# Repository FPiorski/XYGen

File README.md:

# XYgen
### 4 digit numerical diplay using an oscilloscope in XY mode without a microcontroller

#### Work in progress
Soldered everything up, found some bugs, still working on getting them all fixed

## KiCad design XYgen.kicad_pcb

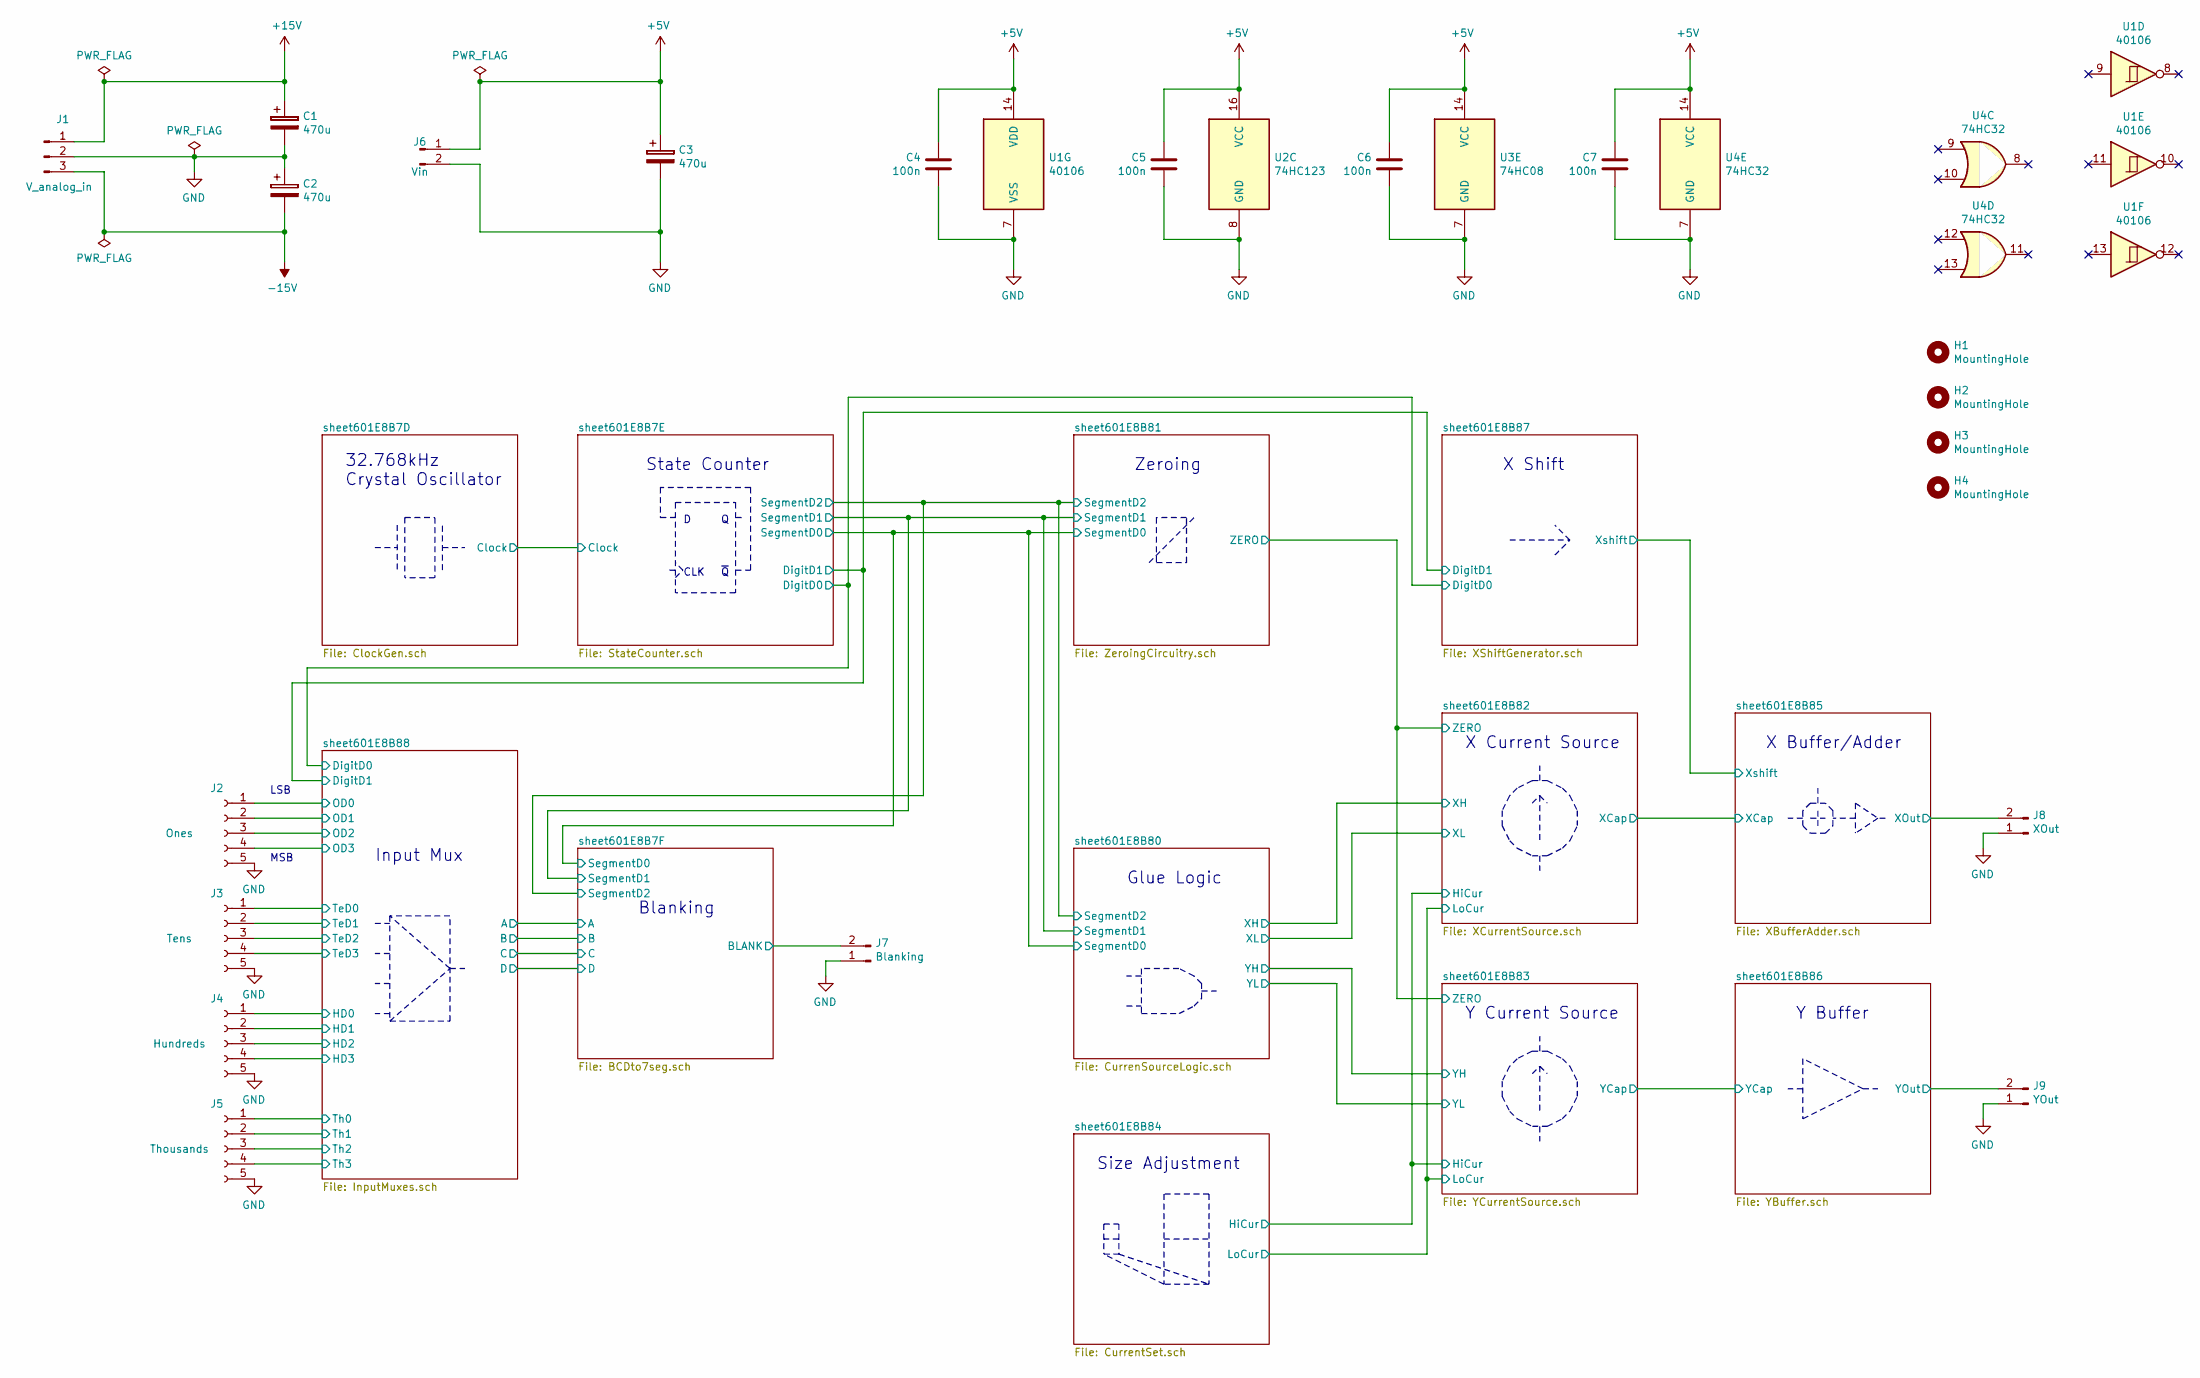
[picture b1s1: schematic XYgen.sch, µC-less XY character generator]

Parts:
C1, C2, C3: 470u; C_1206_3216Metric_Pad1.42x1.75mm_HandSolder
C4, C5, C6, C7: 100n; C_0805_2012Metric_Pad1.15x1.40mm_HandSolder
H1, H2, H3, H4: MountingHole; MountingHole_2.7mm_M2.5
J1: V_analog_in; Molex_KK-254_AE-6410-03A_1x03_P2.54mm_Vertical
J2: Ones; PinSocket_1x05_P2.54mm_Vertical
J3: Tens; PinSocket_1x05_P2.54mm_Vertical
J4: Hundreds; PinSocket_1x05_P2.54mm_Vertical
J5: Thousands; PinSocket_1x05_P2.54mm_Vertical
J6: Vin; Molex_KK-254_AE-6410-02A_1x02_P2.54mm_Vertical
J7: Blanking; PinHeader_1x02_P2.54mm_Vertical
J8: XOut; PinHeader_1x02_P2.54mm_Vertical
J9: YOut; PinHeader_1x02_P2.54mm_Vertical
U1: 40106; TSSOP-14_4.4x5mm_P0.65mm
U2: 74HC123; TSSOP-16_4.4x5mm_P0.65mm
U3: 74HC08; TSSOP-14_4.4x5mm_P0.65mm
U4: 74HC32; TSSOP-14_4.4x5mm_P0.65mm

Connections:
+5V: C3.1, C4.1, C5.1, C6.1, C7.1, J6.1, U1.14 (VDD), U2.16 (VCC), U3.14 (VCC), U4.14 (VCC); also elsewhere on the board
+15V: C1.1, J1.1; also elsewhere on the board
-15V: C2.2, J1.3; also elsewhere on the board
/sheet601E8B7F/BLANK: J7.2; also elsewhere on the board
/sheet601E8B85/XOut: J8.2; also elsewhere on the board
/sheet601E8B86/YOut: J9.2; also elsewhere on the board
/sheet601E8B88/HD0: J4.1; also elsewhere on the board
/sheet601E8B88/HD1: J4.2; also elsewhere on the board
/sheet601E8B88/HD2: J4.3; also elsewhere on the board
/sheet601E8B88/HD3: J4.4; also elsewhere on the board
/sheet601E8B88/OD0: J2.1; also elsewhere on the board
/sheet601E8B88/OD1: J2.2; also elsewhere on the board
/sheet601E8B88/OD2: J2.3; also elsewhere on the board
/sheet601E8B88/OD3: J2.4; also elsewhere on the board
/sheet601E8B88/TeD0: J3.1; also elsewhere on the board
/sheet601E8B88/TeD1: J3.2; also elsewhere on the board
/sheet601E8B88/TeD2: J3.3; also elsewhere on the board
/sheet601E8B88/TeD3: J3.4; also elsewhere on the board
/sheet601E8B88/Th0: J5.1; also elsewhere on the board
/sheet601E8B88/Th1: J5.2; also elsewhere on the board
/sheet601E8B88/Th2: J5.3; also elsewhere on the board
/sheet601E8B88/Th3: J5.4; also elsewhere on the board
GND: C1.2, C2.1, C3.2, C4.2, C5.2, C6.2, C7.2, J1.2, J2.5, J3.5, J4.5, J5.5, J6.2, J7.1, J8.1, J9.1, U1.7 (VSS), U2.8 (GND), U3.7 (GND), U4.7 (GND); also elsewhere on the board

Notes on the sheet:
32.768kHz Crystal Oscillator
CLK
State Counter
LSB
MSB
Zeroing
Input Mux
Blanking
X Shift
Glue Logic
Size Adjustment
X Current Source
Y Current Source
X Buffer/Adder
Y Buffer

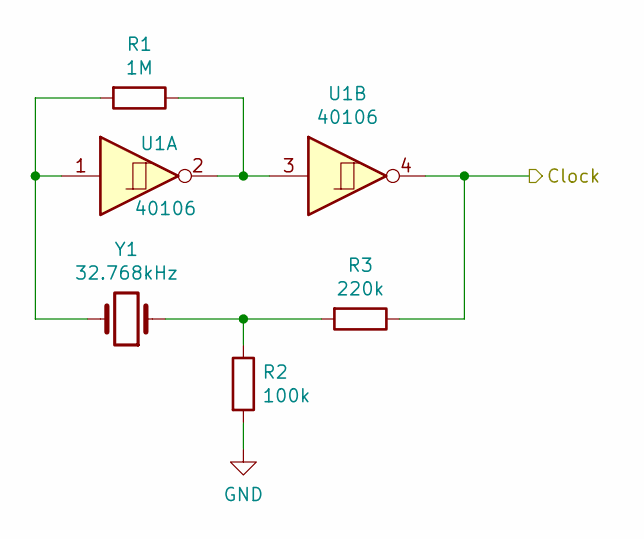
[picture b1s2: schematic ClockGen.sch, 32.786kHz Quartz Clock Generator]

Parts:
R1: 1M; R_0805_2012Metric_Pad1.15x1.40mm_HandSolder
R2: 100k; R_0805_2012Metric_Pad1.15x1.40mm_HandSolder
R3: 220k; R_0805_2012Metric_Pad1.15x1.40mm_HandSolder
U1: 40106; TSSOP-14_4.4x5mm_P0.65mm
Y1: 32.768kHz; Crystal_C26-LF_D2.1mm_L6.5mm_Vertical

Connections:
/sheet601E8B7D/Clock: R3.1, U1.4; also elsewhere on the board
GND: R2.2; also elsewhere on the board
unnamed: R1.1, U1.2, U1.3
unnamed: R1.2, U1.1, Y1.2
unnamed: R2.1, R3.2, Y1.1

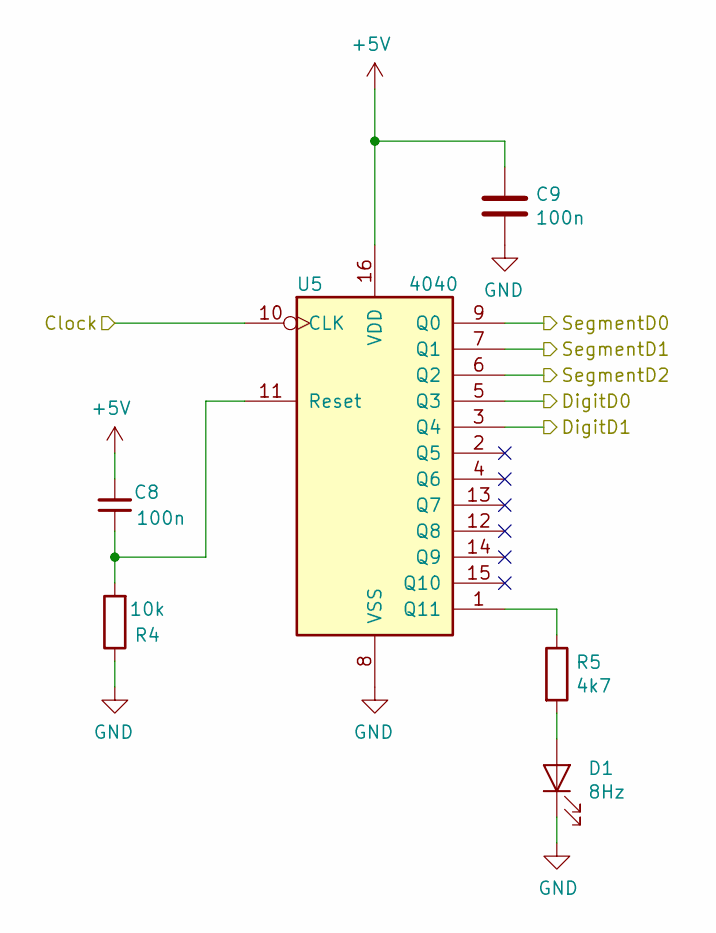
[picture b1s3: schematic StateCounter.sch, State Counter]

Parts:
C8, C9: 100n; C_0805_2012Metric_Pad1.15x1.40mm_HandSolder
D1: 8Hz; LED_0805_2012Metric_Pad1.15x1.40mm_HandSolder
R4: 10k; R_0805_2012Metric_Pad1.15x1.40mm_HandSolder
R5: 4k7; R_0805_2012Metric_Pad1.15x1.40mm_HandSolder
U5: 4040; TSSOP-16_4.4x5mm_P0.65mm

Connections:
+5V: C8.2, C9.1, U5.16 (VDD); also elsewhere on the board
/sheet601E8B7D/Clock: U5.10 (CLK); also elsewhere on the board
/sheet601E8B7E/DigitD0: U5.5 (Q3); also elsewhere on the board
/sheet601E8B7E/DigitD1: U5.3 (Q4); also elsewhere on the board
/sheet601E8B7E/SegmentD0: U5.9 (Q0); also elsewhere on the board
/sheet601E8B7E/SegmentD1: U5.7 (Q1); also elsewhere on the board
/sheet601E8B7E/SegmentD2: U5.6 (Q2); also elsewhere on the board
GND: C9.2, D1.1 (K), R4.1, U5.8 (VSS); also elsewhere on the board
unnamed: C8.1, R4.2, U5.11 (Reset)
unnamed: D1.2 (A), R5.2
unnamed: R5.1, U5.1 (Q11)

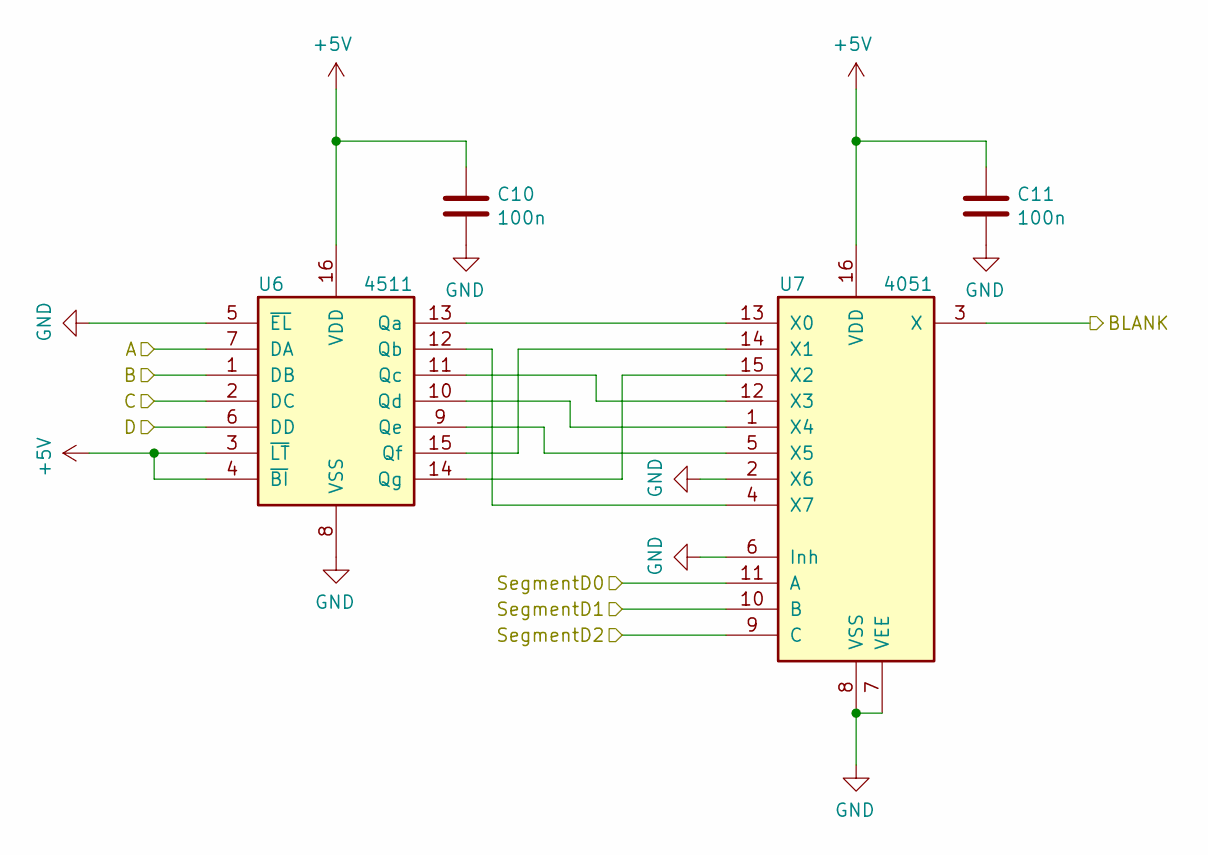
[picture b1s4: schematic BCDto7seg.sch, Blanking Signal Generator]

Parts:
C10, C11: 100n; C_0805_2012Metric_Pad1.15x1.40mm_HandSolder
U6: 4511; SOP-16_4.4x10.4mm_P1.27mm
U7: 4051; TSSOP-16_4.4x5mm_P0.65mm

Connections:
+5V: C10.1, C11.1, U6.3 (~LT), U6.4 (~BI), U6.16 (VDD), U7.16 (VDD); also elsewhere on the board
/sheet601E8B7E/SegmentD0: U7.11 (A); also elsewhere on the board
/sheet601E8B7E/SegmentD1: U7.10 (B); also elsewhere on the board
/sheet601E8B7E/SegmentD2: U7.9 (C); also elsewhere on the board
/sheet601E8B7F/A: U6.7 (DA); also elsewhere on the board
/sheet601E8B7F/B: U6.1 (DB); also elsewhere on the board
/sheet601E8B7F/BLANK: U7.3 (X); also elsewhere on the board
/sheet601E8B7F/C: U6.2 (DC); also elsewhere on the board
/sheet601E8B7F/D: U6.6 (DD); also elsewhere on the board
GND: C10.2, C11.2, U6.5 (~EL), U6.8 (VSS), U7.2 (X6), U7.6 (Inh), U7.7 (VEE), U7.8 (VSS); also elsewhere on the board
unnamed: U6.9 (Qe), U7.5 (X5)
unnamed: U6.10 (Qd), U7.1 (X4)
unnamed: U6.11 (Qc), U7.12 (X3)
unnamed: U6.12 (Qb), U7.4 (X7)
unnamed: U6.13 (Qa), U7.13 (X0)
unnamed: U6.14 (Qg), U7.15 (X2)
unnamed: U6.15 (Qf), U7.14 (X1)

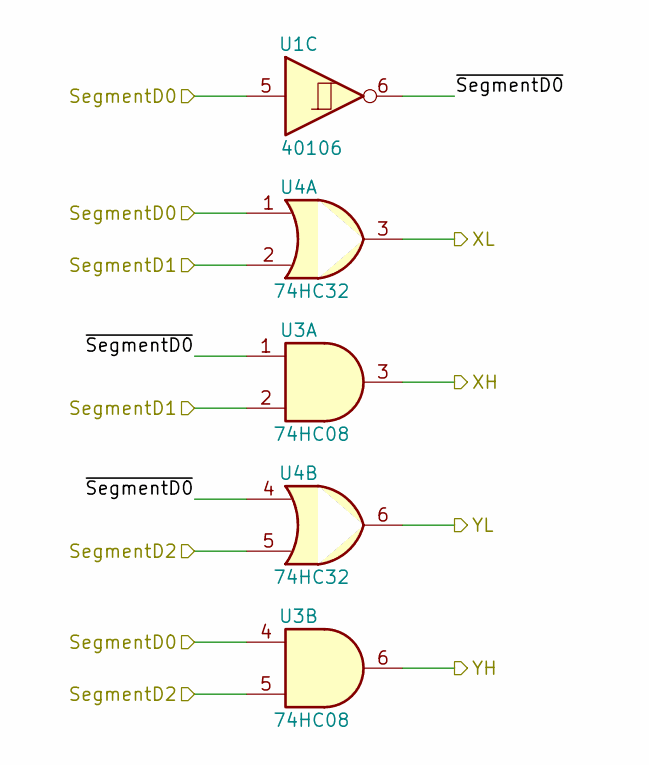
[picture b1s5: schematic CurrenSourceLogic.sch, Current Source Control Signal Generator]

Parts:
U1: 40106; TSSOP-14_4.4x5mm_P0.65mm
U3: 74HC08; TSSOP-14_4.4x5mm_P0.65mm
U4: 74HC32; TSSOP-14_4.4x5mm_P0.65mm

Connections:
/sheet601E8B7E/SegmentD0: U1.5, U3.4, U4.1; also elsewhere on the board
/sheet601E8B7E/SegmentD1: U3.2, U4.2; also elsewhere on the board
/sheet601E8B7E/SegmentD2: U3.5, U4.5; also elsewhere on the board
/sheet601E8B80/XH: U3.3; also elsewhere on the board
/sheet601E8B80/XL: U4.3; also elsewhere on the board
/sheet601E8B80/YH: U3.6; also elsewhere on the board
/sheet601E8B80/YL: U4.6; also elsewhere on the board
/sheet601E8B80/~SegmentD0: U1.6, U3.1, U4.4

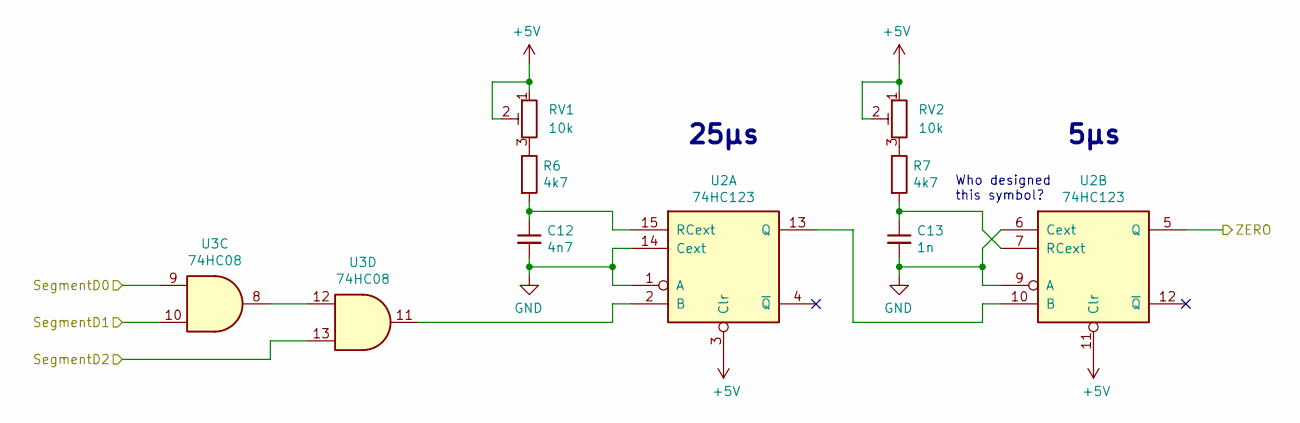
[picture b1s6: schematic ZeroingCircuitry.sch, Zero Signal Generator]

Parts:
C12: 4n7; C_0805_2012Metric_Pad1.15x1.40mm_HandSolder
C13: 1n; C_0805_2012Metric_Pad1.15x1.40mm_HandSolder
R6, R7: 4k7; R_0805_2012Metric_Pad1.15x1.40mm_HandSolder
RV1, RV2: 10k; Potentiometer_Bourns_3296W_Vertical
U2: 74HC123; TSSOP-16_4.4x5mm_P0.65mm
U3: 74HC08; TSSOP-14_4.4x5mm_P0.65mm

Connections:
+5V: RV1.1, RV1.2, RV2.1, RV2.2, U2.3 (Clr), U2.11 (Clr); also elsewhere on the board
/sheet601E8B7E/SegmentD0: U3.9; also elsewhere on the board
/sheet601E8B7E/SegmentD1: U3.10; also elsewhere on the board
/sheet601E8B7E/SegmentD2: U3.13; also elsewhere on the board
/sheet601E8B81/ZERO: U2.5 (Q); also elsewhere on the board
GND: C12.2, C13.2, U2.1 (A), U2.6 (Cext), U2.9 (A), U2.14 (Cext); also elsewhere on the board
unnamed: C12.1, R6.2, U2.15 (RCext)
unnamed: C13.1, R7.2, U2.7 (RCext)
unnamed: R6.1, RV1.3
unnamed: R7.1, RV2.3
unnamed: U2.2 (B), U3.11
unnamed: U2.10 (B), U2.13 (Q)
unnamed: U3.8, U3.12

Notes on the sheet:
25µs
5µs
Who designed this symbol?

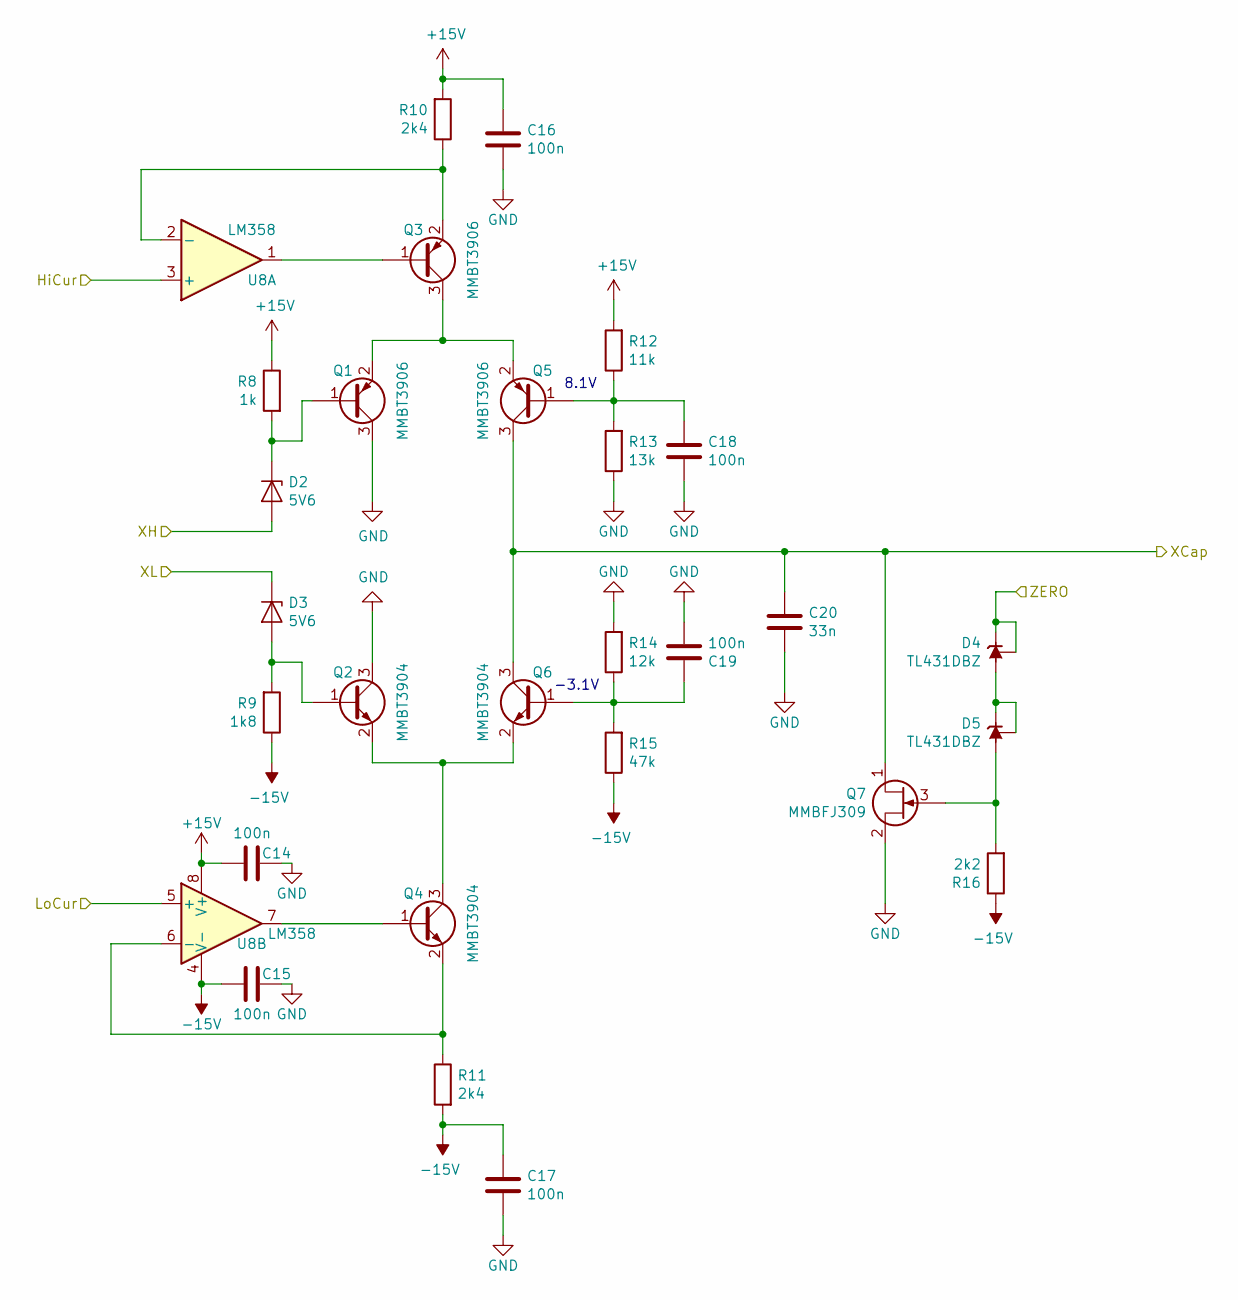
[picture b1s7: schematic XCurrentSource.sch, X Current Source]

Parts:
C14, C15, C16, C17, C18, C19: 100n; C_0805_2012Metric_Pad1.15x1.40mm_HandSolder
C20: 33n; C_0805_2012Metric_Pad1.15x1.40mm_HandSolder
D2, D3: 5V6; D_SOD-123
D4, D5: TL431DBZ; SOT-23
Q1, Q3, Q5: MMBT3906; SOT-23
Q2, Q4, Q6: MMBT3904; SOT-23
Q7: MMBFJ309; SOT-23
R8: 1k; R_0805_2012Metric_Pad1.15x1.40mm_HandSolder
R9: 1k8; R_0805_2012Metric_Pad1.15x1.40mm_HandSolder
R10, R11: 2k4; R_0805_2012Metric_Pad1.15x1.40mm_HandSolder
R12: 11k; R_0805_2012Metric_Pad1.15x1.40mm_HandSolder
R13: 13k; R_0805_2012Metric_Pad1.15x1.40mm_HandSolder
R14: 12k; R_0805_2012Metric_Pad1.15x1.40mm_HandSolder
R15: 47k; R_0805_2012Metric_Pad1.15x1.40mm_HandSolder
R16: 2k2; R_0805_2012Metric_Pad1.15x1.40mm_HandSolder
U8: LM358; SOIC-8_3.9x4.9mm_P1.27mm

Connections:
+15V: C14.1, C16.1, R8.1, R10.2, R12.2, U8.8 (V+); also elsewhere on the board
-15V: C15.1, C17.1, R9.1, R11.2, R15.1, R16.1, U8.4 (V-); also elsewhere on the board
/sheet601E8B80/XH: D2.2 (A); also elsewhere on the board
/sheet601E8B80/XL: D3.1 (K); also elsewhere on the board
/sheet601E8B81/ZERO: D4.1 (K), D4.2 (REF); also elsewhere on the board
/sheet601E8B82/HiCur: U8.3 (+); also elsewhere on the board
/sheet601E8B82/LoCur: U8.5 (+); also elsewhere on the board
/sheet601E8B82/XCap: C20.1, Q5.3 (C), Q6.3 (C), Q7.1 (D); also elsewhere on the board
GND: C14.2, C15.2, C16.2, C17.2, C18.2, C19.2, C20.2, Q1.3 (C), Q2.3 (C), Q7.2 (S), R13.1, R14.2; also elsewhere on the board
unnamed: C18.1, Q5.1 (B), R12.1, R13.2
unnamed: C19.1, Q6.1 (B), R14.1, R15.2
unnamed: D2.1 (K), Q1.1 (B), R8.2
unnamed: D3.2 (A), Q2.1 (B), R9.2
unnamed: D4.3 (A), D5.1 (K), D5.2 (REF)
unnamed: D5.3 (A), Q7.3 (G), R16.2
unnamed: Q1.2 (E), Q3.3 (C), Q5.2 (E)
unnamed: Q2.2 (E), Q4.3 (C), Q6.2 (E)
unnamed: Q3.1 (B), U8.1
unnamed: Q3.2 (E), R10.1, U8.2 (-)
unnamed: Q4.1 (B), U8.7
unnamed: Q4.2 (E), R11.1, U8.6 (-)

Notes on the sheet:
8.1V
-3.1V

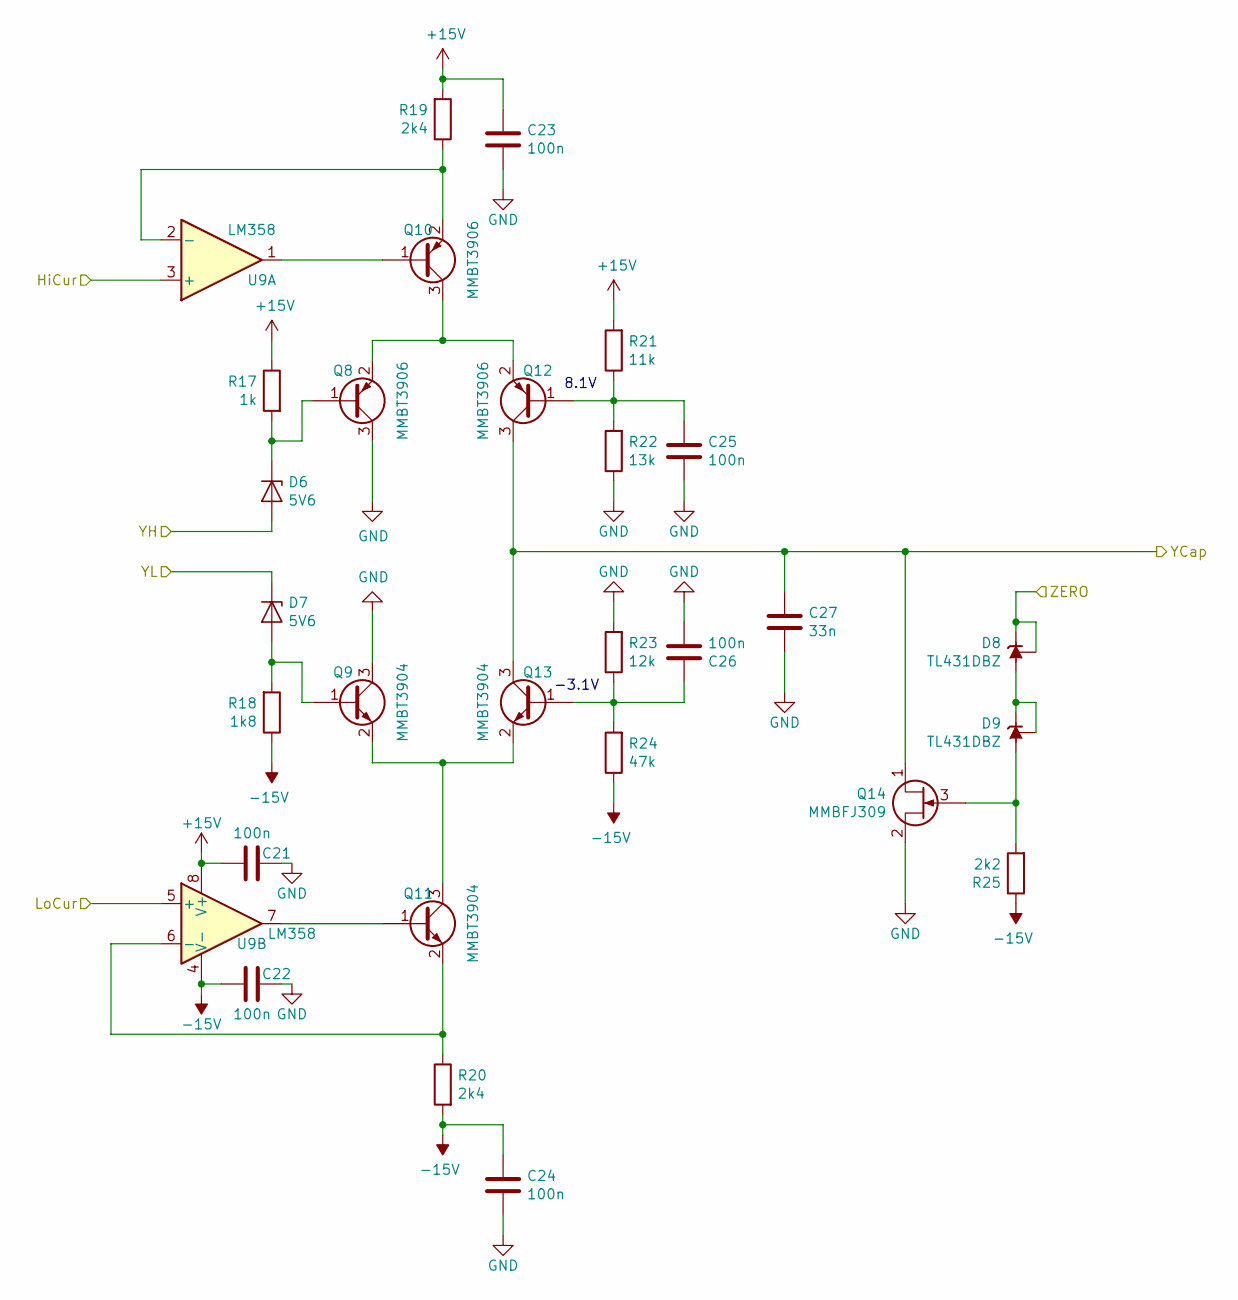
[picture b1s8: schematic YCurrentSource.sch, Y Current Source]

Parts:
C21, C22, C23, C24, C25, C26: 100n; C_0805_2012Metric_Pad1.15x1.40mm_HandSolder
C27: 33n; C_0805_2012Metric_Pad1.15x1.40mm_HandSolder
D6, D7: 5V6; D_SOD-123
D8, D9: TL431DBZ; SOT-23
Q8, Q10, Q12: MMBT3906; SOT-23
Q9, Q11, Q13: MMBT3904; SOT-23
Q14: MMBFJ309; SOT-23
R17: 1k; R_0805_2012Metric_Pad1.15x1.40mm_HandSolder
R18: 1k8; R_0805_2012Metric_Pad1.15x1.40mm_HandSolder
R19, R20: 2k4; R_0805_2012Metric_Pad1.15x1.40mm_HandSolder
R21: 11k; R_0805_2012Metric_Pad1.15x1.40mm_HandSolder
R22: 13k; R_0805_2012Metric_Pad1.15x1.40mm_HandSolder
R23: 12k; R_0805_2012Metric_Pad1.15x1.40mm_HandSolder
R24: 47k; R_0805_2012Metric_Pad1.15x1.40mm_HandSolder
R25: 2k2; R_0805_2012Metric_Pad1.15x1.40mm_HandSolder
U9: LM358; SOIC-8_3.9x4.9mm_P1.27mm

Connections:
+15V: C21.1, C23.1, R17.1, R19.2, R21.2, U9.8 (V+); also elsewhere on the board
-15V: C22.1, C24.1, R18.1, R20.2, R24.1, R25.1, U9.4 (V-); also elsewhere on the board
/sheet601E8B80/YH: D6.2 (A); also elsewhere on the board
/sheet601E8B80/YL: D7.1 (K); also elsewhere on the board
/sheet601E8B81/ZERO: D8.1 (K), D8.2 (REF); also elsewhere on the board
/sheet601E8B82/HiCur: U9.3 (+); also elsewhere on the board
/sheet601E8B82/LoCur: U9.5 (+); also elsewhere on the board
/sheet601E8B83/YCap: C27.1, Q12.3 (C), Q13.3 (C), Q14.1 (D); also elsewhere on the board
GND: C21.2, C22.2, C23.2, C24.2, C25.2, C26.2, C27.2, Q8.3 (C), Q9.3 (C), Q14.2 (S), R22.1, R23.2; also elsewhere on the board
unnamed: C25.1, Q12.1 (B), R21.1, R22.2
unnamed: C26.1, Q13.1 (B), R23.1, R24.2
unnamed: D6.1 (K), Q8.1 (B), R17.2
unnamed: D7.2 (A), Q9.1 (B), R18.2
unnamed: D8.3 (A), D9.1 (K), D9.2 (REF)
unnamed: D9.3 (A), Q14.3 (G), R25.2
unnamed: Q10.1 (B), U9.1
unnamed: Q10.2 (E), R19.1, U9.2 (-)
unnamed: Q8.2 (E), Q10.3 (C), Q12.2 (E)
unnamed: Q11.1 (B), U9.7
unnamed: Q11.2 (E), R20.1, U9.6 (-)
unnamed: Q9.2 (E), Q11.3 (C), Q13.2 (E)

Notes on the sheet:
8.1V
-3.1V

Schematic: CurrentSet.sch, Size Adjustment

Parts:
Q15: MMBT3904; SOT-23
R26: 43k; R_0805_2012Metric_Pad1.15x1.40mm_HandSolder
R27: 4k7; R_0805_2012Metric_Pad1.15x1.40mm_HandSolder
R28, R29: 2k4; R_0805_2012Metric_Pad1.15x1.40mm_HandSolder
RV3: 10k; Potentiometer_Bourns_3296W_Vertical
U10: LM358; SOIC-8_3.9x4.9mm_P1.27mm

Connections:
+15V: R28.2; also elsewhere on the board
-15V: R27.1, R29.2; also elsewhere on the board
/sheet601E8B82/HiCur: Q15.3 (C), R28.1; also elsewhere on the board
/sheet601E8B82/LoCur: Q15.2 (E), R29.1, U10.6 (-); also elsewhere on the board
GND: R26.2; also elsewhere on the board
unnamed: Q15.1 (B), U10.7
unnamed: R26.1, RV3.2, RV3.3, U10.5 (+)
unnamed: R27.2, RV3.1

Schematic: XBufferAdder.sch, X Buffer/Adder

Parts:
C28, C29, C30: 100n; C_0805_2012Metric_Pad1.15x1.40mm_HandSolder
R30: 1M; R_0805_2012Metric_Pad1.15x1.40mm_HandSolder
R31, R32, R33: 10k; R_0805_2012Metric_Pad1.15x1.40mm_HandSolder
U11: NE5532; SOIC-8_3.9x4.9mm_P1.27mm

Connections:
+15V: C29.1, U11.8 (V+); also elsewhere on the board
-15V: C30.1, U11.4 (V-); also elsewhere on the board
/sheet601E8B82/XCap: C28.1; also elsewhere on the board
/sheet601E8B85/XOut: R33.1, U11.7; also elsewhere on the board
/sheet601E8B85/Xshift: R32.1; also elsewhere on the board
GND: C29.2, C30.2, R30.2, U11.5 (+); also elsewhere on the board
unnamed: C28.2, R30.1, U11.3 (+)
unnamed: R31.1, R32.2, R33.2, U11.6 (-)
unnamed: R31.2, U11.1, U11.2 (-)

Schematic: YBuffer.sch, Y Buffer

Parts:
C31, C32, C33: 100n; C_0805_2012Metric_Pad1.15x1.40mm_HandSolder
R34: 1M; R_0805_2012Metric_Pad1.15x1.40mm_HandSolder
U12: NE5532; SOIC-8_3.9x4.9mm_P1.27mm

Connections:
+15V: C32.1, U12.8 (V+); also elsewhere on the board
-15V: C33.1, U12.4 (V-); also elsewhere on the board
/sheet601E8B83/YCap: C31.1; also elsewhere on the board
/sheet601E8B86/YOut: U12.1, U12.2 (-); also elsewhere on the board
GND: C32.2, C33.2, R34.2; also elsewhere on the board
unnamed: C31.2, R34.1, U12.3 (+)

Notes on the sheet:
Y buffer

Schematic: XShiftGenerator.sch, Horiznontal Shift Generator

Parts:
C34, C35: 100n; C_0805_2012Metric_Pad1.15x1.40mm_HandSolder
R35: 2k; R_0805_2012Metric_Pad1.15x1.40mm_HandSolder
R36: 1k; R_0805_2012Metric_Pad1.15x1.40mm_HandSolder
RV4: 1k; Potentiometer_Bourns_3296W_Vertical
U10: LM358; SOIC-8_3.9x4.9mm_P1.27mm

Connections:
+15V: C34.1, U10.8 (V+); also elsewhere on the board
-15V: C35.1, U10.4 (V-); also elsewhere on the board
/sheet601E8B7E/DigitD0: R35.1; also elsewhere on the board
/sheet601E8B7E/DigitD1: R36.2; also elsewhere on the board
/sheet601E8B85/Xshift: RV4.1, RV4.2, U10.1; also elsewhere on the board
GND: C34.2, C35.2, U10.3 (+); also elsewhere on the board
unnamed: R35.2, R36.1, RV4.3, U10.2 (-)

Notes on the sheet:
2-bit DAC for horizontal shift

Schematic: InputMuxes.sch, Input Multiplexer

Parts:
C36, C37: 100n; C_0805_2012Metric_Pad1.15x1.40mm_HandSolder
U13, U14: 4052; TSSOP-16_4.4x5mm_P0.65mm

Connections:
+5V: C36.1, C37.1, U13.16 (VDD), U14.16 (VDD); also elsewhere on the board
/sheet601E8B7E/DigitD0: U13.10 (A), U14.10 (A); also elsewhere on the board
/sheet601E8B7E/DigitD1: U13.9 (B), U14.9 (B); also elsewhere on the board
/sheet601E8B7F/A: U13.13 (X); also elsewhere on the board
/sheet601E8B7F/B: U13.3 (Y); also elsewhere on the board
/sheet601E8B7F/C: U14.13 (X); also elsewhere on the board
/sheet601E8B7F/D: U14.3 (Y); also elsewhere on the board
/sheet601E8B88/HD0: U13.15 (X2); also elsewhere on the board
/sheet601E8B88/HD1: U13.2 (Y2); also elsewhere on the board
/sheet601E8B88/HD2: U14.15 (X2); also elsewhere on the board
/sheet601E8B88/HD3: U14.2 (Y2); also elsewhere on the board
/sheet601E8B88/OD0: U13.12 (X0); also elsewhere on the board
/sheet601E8B88/OD1: U13.1 (Y0); also elsewhere on the board
/sheet601E8B88/OD2: U14.12 (X0); also elsewhere on the board
/sheet601E8B88/OD3: U14.1 (Y0); also elsewhere on the board
/sheet601E8B88/TeD0: U13.14 (X1); also elsewhere on the board
/sheet601E8B88/TeD1: U13.5 (Y1); also elsewhere on the board
/sheet601E8B88/TeD2: U14.14 (X1); also elsewhere on the board
/sheet601E8B88/TeD3: U14.5 (Y1); also elsewhere on the board
/sheet601E8B88/Th0: U13.11 (X3); also elsewhere on the board
/sheet601E8B88/Th1: U13.4 (Y3); also elsewhere on the board
/sheet601E8B88/Th2: U14.11 (X3); also elsewhere on the board
/sheet601E8B88/Th3: U14.4 (Y3); also elsewhere on the board
GND: C36.2, C37.2, U13.6 (Inh), U13.7 (VEE), U13.8 (VSS), U14.6 (Inh), U14.7 (VEE), U14.8 (VSS); also elsewhere on the board

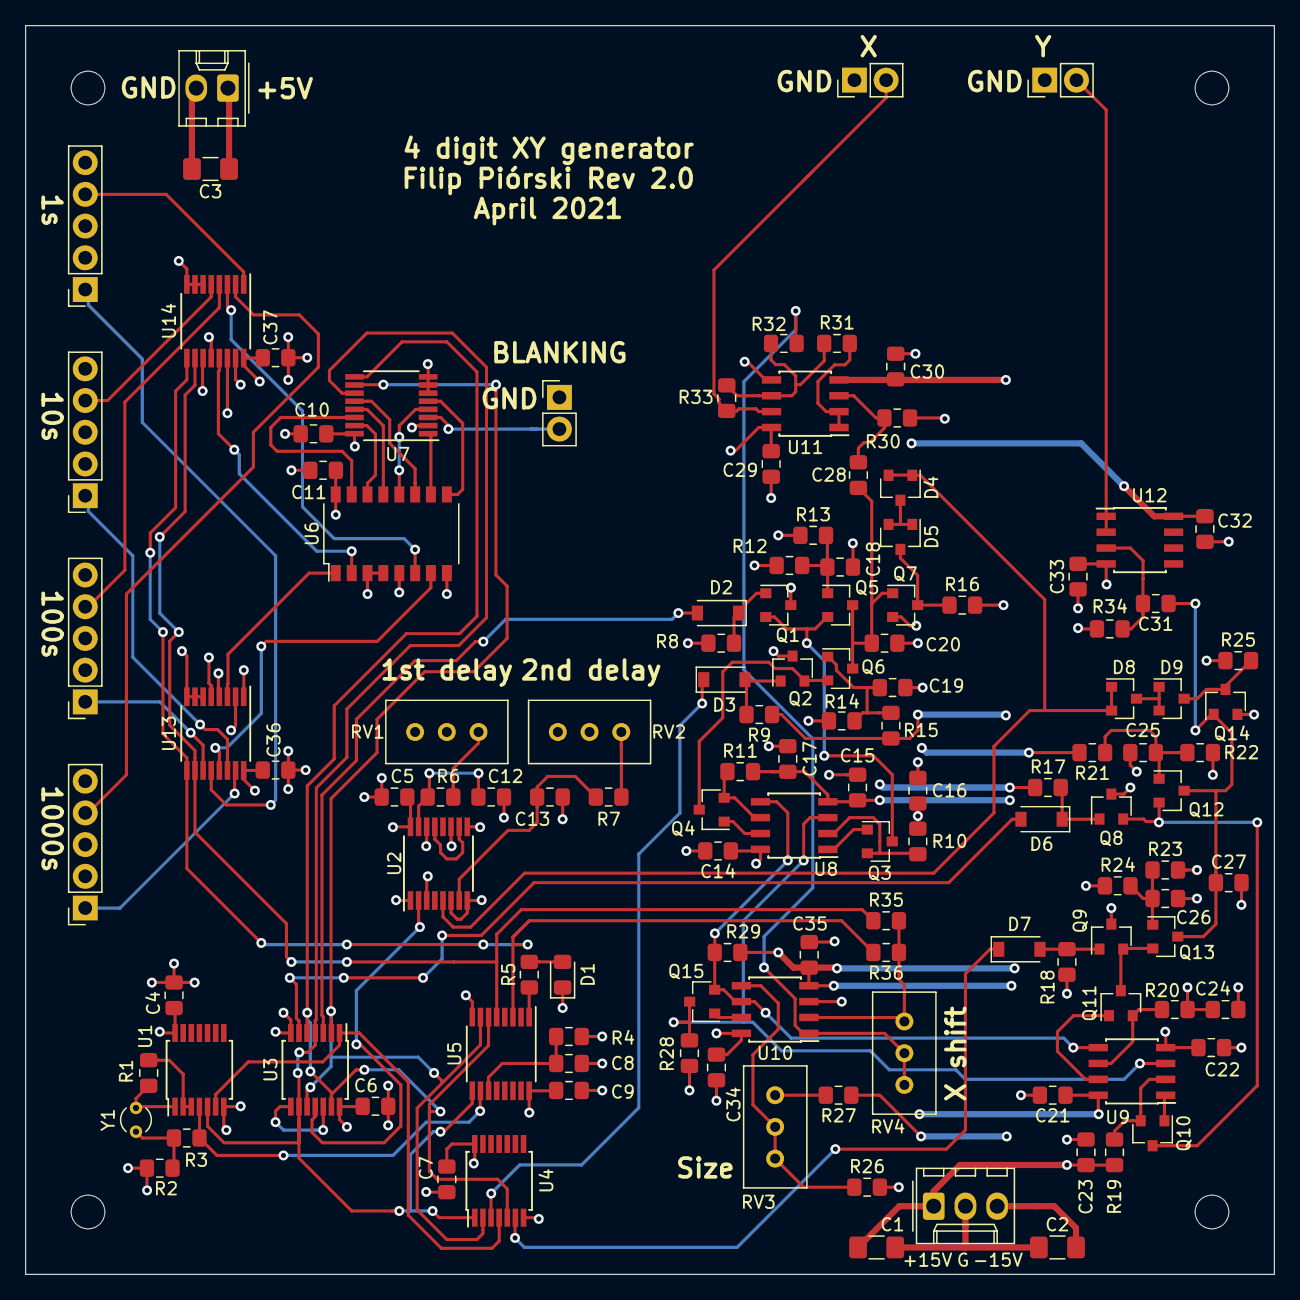
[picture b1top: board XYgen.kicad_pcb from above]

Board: 4 copper layers, 100.0 x 100.0 mm, 129 parts (0 on the bottom side), 96 nets.

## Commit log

2021-04-20 Fixed some bugs, finished block symbols
